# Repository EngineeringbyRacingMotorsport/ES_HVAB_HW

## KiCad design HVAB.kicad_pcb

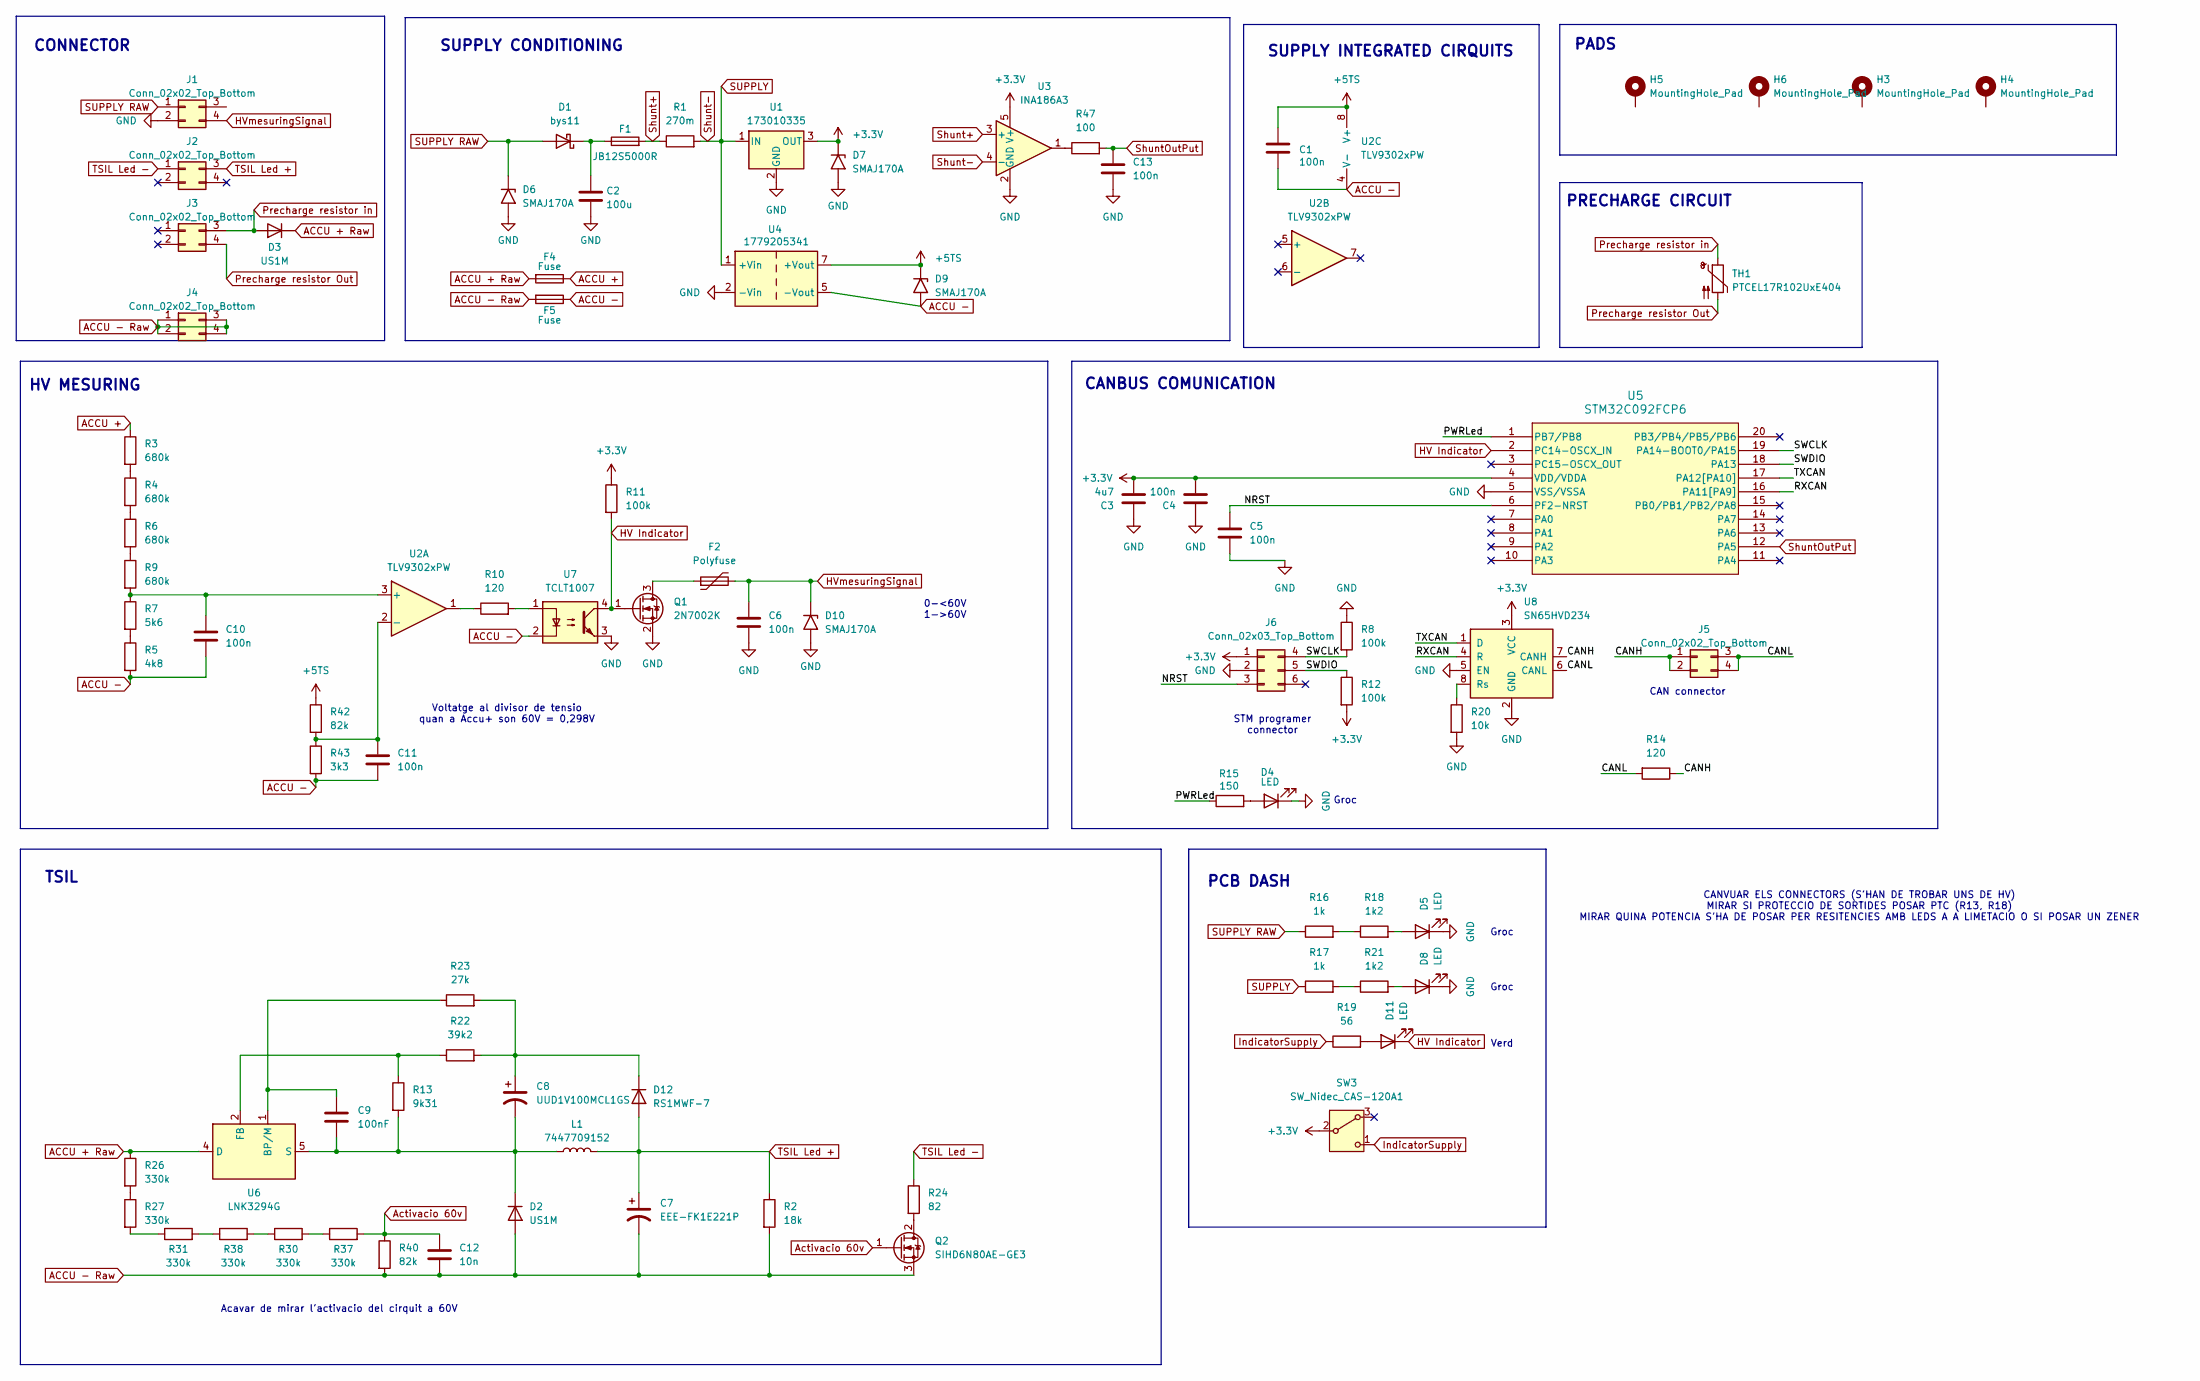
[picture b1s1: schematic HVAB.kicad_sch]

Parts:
C1, C4, C5, C6, C10, C11, C13: 100n; C_0603_1608Metric
C2: 100u; CP_Elec_10x10
C3: 4u7; C_0603_1608Metric
C7: EEE-FK1E221P; C_Elec_8x10.2
C8: UUD1V100MCL1GS; CP_Elec_5x5.8
C9: 100nF; C_0603_1608Metric
C12: 10n; C_0603_1608Metric
D1: bys11; D_SMA
D2, D3: US1M; D_SMA
D4, D5, D8, D11: LED; LED_0603_1608Metric
D6, D7, D9, D10: SMAJ170A; D_SMB
D12: RS1MWF-7; DIO_PMEG2010AEH_115
F1: JB12S5000R; Fuse_1206_3216Metric
F2: Polyfuse; Fuse_0603_1608Metric
F4, F5: Fuse; FUSE_0ACJ-1000-TE
H3, H4, H5, H6: MountingHole_Pad; MountingHole_3.5mm
J1, J5: Conn_02x02_Top_Bottom; Molex_Nano-Fit_105310-xx04_2x02_P2.50mm_Vertical
J2, J3, J4: Conn_02x02_Top_Bottom; 2068320401
J6: Conn_02x03_Top_Bottom; PinSocket_2x03_P1.27mm_Vertical_SMD
L1: 7447709152; L_Wuerth_WE-PD-Typ-LS
Q1: 2N7002K; SOT-23
Q2: SIHD6N80AE-GE3; TO-252-2
R1: 270m; R_0603_1608Metric
R2: 18k; R_0603_1608Metric
R3, R4, R6, R9: 680k; R_1206_3216Metric
R5: 4k8; R_0603_1608Metric
R7: 5k6; R_0603_1608Metric
R8, R11, R12: 100k; R_0603_1608Metric
R10, R14: 120; R_0603_1608Metric
R13: 9k31; R_0603_1608Metric
R15: 150; R_0603_1608Metric
R16, R17: 1k; R_1206_3216Metric
R18, R21: 1k2; R_1206_3216Metric
R19: 56; R_0603_1608Metric
R20: 10k; R_0603_1608Metric
R22: 39k2; R_0603_1608Metric
R23: 27k; R_0603_1608Metric
R24: 82; R_0603_1608Metric
R26, R27, R30, R31, R37, R38: 330k; R_1206_3216Metric
R40, R42: 82k; R_0603_1608Metric
R43: 3k3; R_0603_1608Metric
R47: 100; R_0603_1608Metric
SW3: SW_Nidec_CAS-120A1; Nidec_Copal_CAS-120A
TH1: PTCEL17R102UxE404; PTCEL17R501TBE
U1: 173010335; Converter_DCDC_RECOM_R-78E-0.5_THT
U2: TLV9302xPW; TSSOP-8_4.4x3mm_P0.65mm
U3: INA186A3; SOT-23-5
U4: 1779205341; Converter_DCDC_TRACO_TEA1-xxxxHI_THT
U5: STM32C092FCP6; TSSOP-20_4.4x6.5mm_P0.65mm
U6: LNK3294G; PowerIntegrations_SMD-8C
U7: TCLT1007; SOP-4_7.5x4.1mm_P2.54mm
U8: SN65HVD234; SOIC-8_3.9x4.9mm_P1.27mm

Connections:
+3.3V: C3.2, C4.2, D7.1 (A1), J6.1, R11.1, R12.2, SW3.2 (B), U1.3 (OUT), U3.5 (V+), U5.4 (VDD/VDDA), U8.3 (VCC)
+5TS: C1.1, D9.1 (A1), R42.1, U2.8 (V+), U4.7 (+Vout)
/CANH: J5.1, J5.2, R14.1, U8.7 (CANH)
/CANL: J5.3, J5.4, R14.2, U8.6 (CANL)
/NRST: C5.1, J6.3, U5.6 (PF2-NRST)
/PWRLed: R15.1, U5.1 (PB7/PB8)
/RXCAN: U5.16 (PA11[PA9]), U8.4 (R)
/SWCLK: J6.4, R8.2, U5.19 (PA14-BOOT0/PA15)
/SWDIO: J6.5, R12.1, U5.18 (PA13)
/TXCAN: U5.17 (PA12[PA10]), U8.1 (D)
ACCU +: F4.1, R3.1
ACCU + Raw: D3.1 (K), F4.2, R26.1, U6.4 (D)
ACCU -: C1.2, C10.2, C11.2, D9.2 (A2), F5.1, R5.2, R43.2, U2.4 (V-), U4.5 (-Vout), U7.2
ACCU - Raw: C7.2, C12.2, D2.2 (A), F5.2, J4.1, J4.2, J4.3, J4.4, Q2.3 (S), R2.2, R40.2
Activacio 60v: C12.1, Q2.1 (G), R37.2, R40.1
GND: C2.2, C3.1, C4.1, C5.2, C6.2, C13.2, D4.1 (K), D5.1 (K), D6.2 (A2), D7.2 (A2), D8.1 (K), D10.2 (A2), J1.2, J6.2, Q1.2 (S), R8.1, R20.2, U1.2 (GND), U3.2 (GND), U4.2 (-Vin), U5.5 (VSS/VSSA), U7.3, U8.2 (GND), U8.5 (EN)
HV Indicator: D11.1 (K), Q1.1 (G), R11.2, U5.2 (PC14-OSCX_IN), U7.4
HVmesuringSignal: C6.1, D10.1 (A1), F2.2, J1.4
IndicatorSupply: R19.1, SW3.1 (C)
unnamed: C2.1, D1.1 (K), F1.1
unnamed: C8.2, C9.2, D2.1 (K), L1.1, R13.2, U6.5 (S), U6.6 (S), U6.7 (S), U6.8 (S)
unnamed: D4.2 (A), R15.2
unnamed: D5.2 (A), R18.2
unnamed: D8.2 (A), R21.2
unnamed: D11.2 (A), R19.2
unnamed: C8.1, D12.1 (K), R22.2, R23.2
unnamed: F2.1, Q1.3 (D)
unnamed: Q2.2 (D), R24.2
unnamed: R3.2, R4.1
unnamed: R4.2, R6.1
unnamed: R5.1, R7.2
unnamed: R6.2, R9.1
unnamed: R10.1, U2.1
unnamed: R10.2, U7.1
unnamed: R16.2, R18.1
unnamed: R17.2, R21.1
unnamed: R26.2, R27.1
unnamed: R27.2, R31.1
unnamed: R30.1, R38.2
unnamed: R30.2, R37.1
unnamed: R31.2, R38.1
unnamed: R47.1, U3.1
unnamed: C10.1, R7.1, R9.2, U2.3 (+)
unnamed: C11.1, R42.2, R43.1, U2.2 (-)
unnamed: C9.1, R23.1, U6.1 (BP/M)
unnamed: R13.1, R22.1, U6.2 (FB)
unnamed: R20.1, U8.8 (Rs)
Precharge resistor Out: J3.4, TH1.2
Precharge resistor in: D3.2 (A), J3.3, TH1.1
SUPPLY: R1.2, R17.1, U1.1 (IN), U3.4 (-), U4.1 (+Vin)
SUPPLY RAW: D1.2 (A), D6.1 (A1), J1.1, R16.1
Shunt+: F1.2, R1.1, U3.3 (+)
ShuntOutPut: C13.1, R47.2, U5.12 (PA5)
TSIL Led +: C7.1, D12.2 (A), J2.3, L1.2, R2.1
TSIL Led -: J2.1, R24.1

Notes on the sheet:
PADS
CANBUS COMUNICATION
Groc
Verd
TSIL
SUPPLY INTEGRATED CIRQUITS
Voltatge al divisor de tensio quan a Accu+ son 60V = 0,298V
CANVUAR ELS CONNECTORS (S'HAN DE TROBAR UNS DE HV) MIRAR SI PROTECCIO DE SORTIDES POSAR PTC (R13, R18) MIRAR QUINA POTENCIA S'HA DE POSAR PER RESITENCIES AMB LEDS A A LIMETACIO O SI POSAR UN ZENER
CAN connector
PCB DASH
PRECHARGE CIRCUIT
SUPPLY CONDITIONING
0-<60V 1->60V
STM programer connector
CONNECTOR
HV MESURING
Acavar de mirar l'activacio del cirquit a 60V

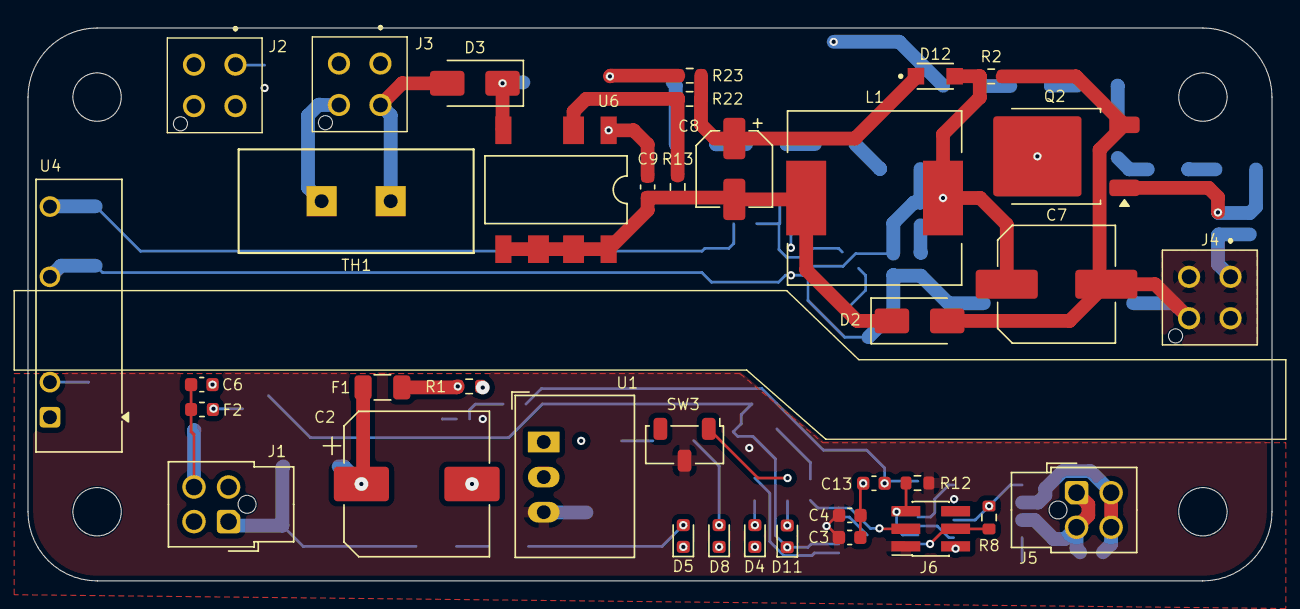
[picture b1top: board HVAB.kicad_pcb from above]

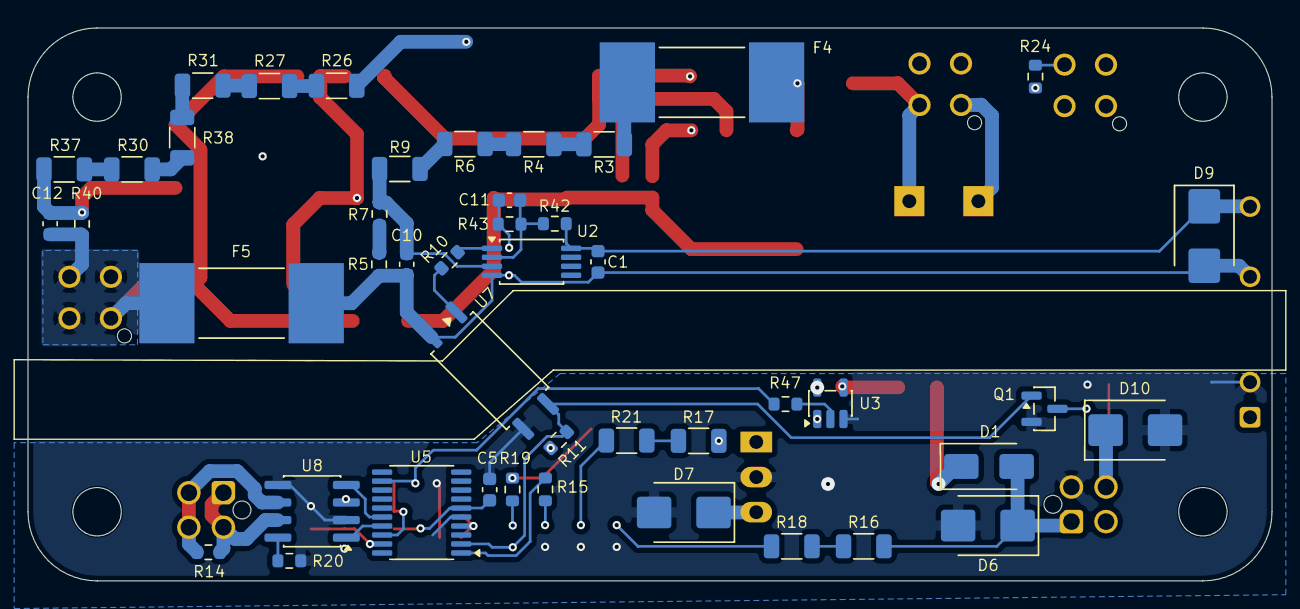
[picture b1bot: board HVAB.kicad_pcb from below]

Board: 4 copper layers, 90.0 x 40.0 mm, 86 parts (45 on the bottom side), 55 nets.
